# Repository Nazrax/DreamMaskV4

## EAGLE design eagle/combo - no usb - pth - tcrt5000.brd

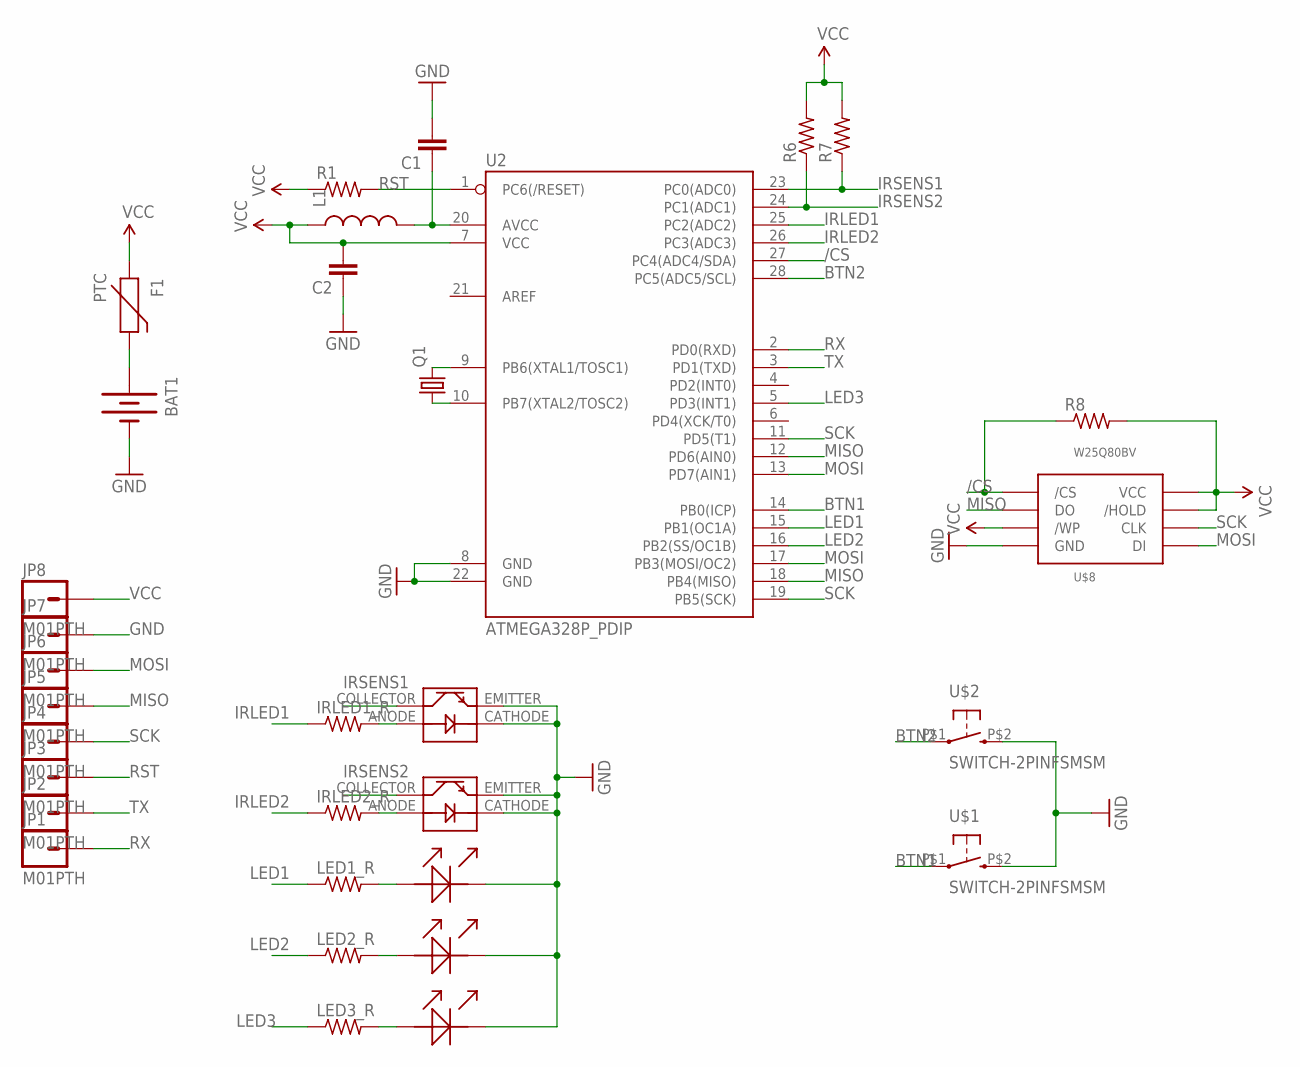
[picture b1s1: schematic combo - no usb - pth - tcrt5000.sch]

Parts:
BAT1: BATTERYBA2032SM; BA2032SM
C1, C2: CAP0805; 0805
F1: PTC; R0805
IRLED1_R, IRLED2_R: R-US_M0805; M0805
JP1, JP2, JP3, JP4, JP5, JP6, JP7, JP8: M01PTH; 1X01
L1: INDUCTOR0805; 0805
LED1_R, LED2_R, LED3_R: R-US_M0805; M0805
Q1: CRYSTALTC26V; TC26V
R1, R6, R7, R8: R-US_M0805; M0805
U2: ATMEGA328P_PDIP; DIL28-3
U$1, U$2: SWITCH-2PINFSMSM; FSMSM-BUTTON
U$3, U$4: IR_SENSORTCRT5000; TCRT5000
U$5, U$6: LEDPTH; LED
U$7: LED0603; 0603
U$8: W25Q80BVSOIC-08; W25Q80BV-SOIC-208MIL

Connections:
/CS: R8.1, U2.27 (PC4(ADC4/SDA)), U$8./CS
BTN1: U2.14 (PB0(ICP)), U$1.P$1 (1)
BTN2: U2.28 (PC5(ADC5/SCL)), U$2.P$1 (1)
GND: BAT1.-, C1.2, C2.1, JP7.1, U2.8 (GND), U2.22 (GND), U$1.P$2 (3), U$2.P$2 (3), U$3.CATHODE (LED-), U$3.EMITTER, U$4.CATHODE (LED-), U$4.EMITTER, U$5.-, U$6.-, U$7.2 (-), U$8.GND
IRLED1: IRLED1_R.1, U2.25 (PC2(ADC2))
IRLED2: IRLED2_R.1, U2.26 (PC3(ADC3))
IRSENS1: R7.1, U2.23 (PC0(ADC0)), U$3.COLLECTOR
IRSENS2: R6.1, U2.24 (PC1(ADC1)), U$4.COLLECTOR
LED1: LED1_R.1, U2.15 (PB1(OC1A))
LED2: LED2_R.1, U2.16 (PB2(SS/OC1B))
LED3: LED3_R.1, U2.5 (PD3(INT1))
MISO: JP5.1, U2.12 (PD6(AIN0)), U2.18 (PB4(MISO)), U$8.DO
MOSI: JP6.1, U2.13 (PD7(AIN1)), U2.17 (PB3(MOSI/OC2)), U$8.DI
unnamed: BAT1.+, F1.2
unnamed: Q1.2, U2.9 (PB6(XTAL1/TOSC1))
unnamed: Q1.1, U2.10 (PB7(XTAL2/TOSC2))
unnamed: C1.1, L1.2, U2.20 (AVCC)
unnamed: LED3_R.2, U$7.1 (+)
unnamed: LED2_R.2, U$6.+
unnamed: LED1_R.2, U$5.+
unnamed: IRLED2_R.2, U$4.ANODE (LED+)
unnamed: IRLED1_R.2, U$3.ANODE (LED+)
RST: JP3.1, R1.2, U2.1 (PC6(/RESET))
RX: JP1.1, U2.2 (PD0(RXD))
SCK: JP4.1, U2.11 (PD5(T1)), U2.19 (PB5(SCK)), U$8.CLK
TX: JP2.1, U2.3 (PD1(TXD))
VCC: C2.2, F1.1, JP8.1, L1.1, R1.1, R6.2, R7.2, R8.2, U2.7 (VCC), U$8./HOLD, U$8./WP, U$8.VCC

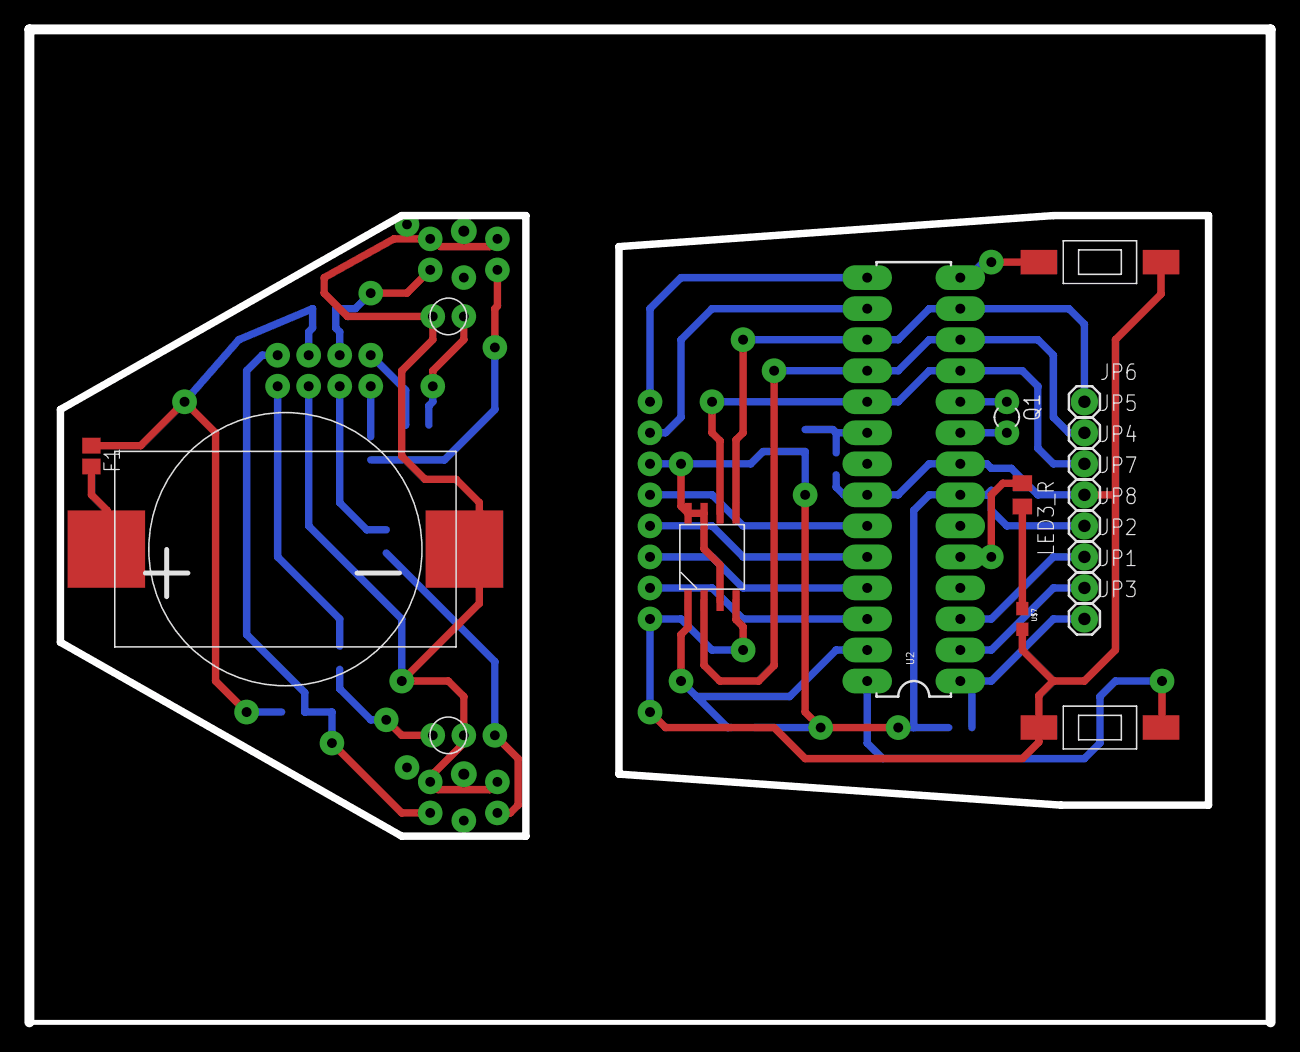
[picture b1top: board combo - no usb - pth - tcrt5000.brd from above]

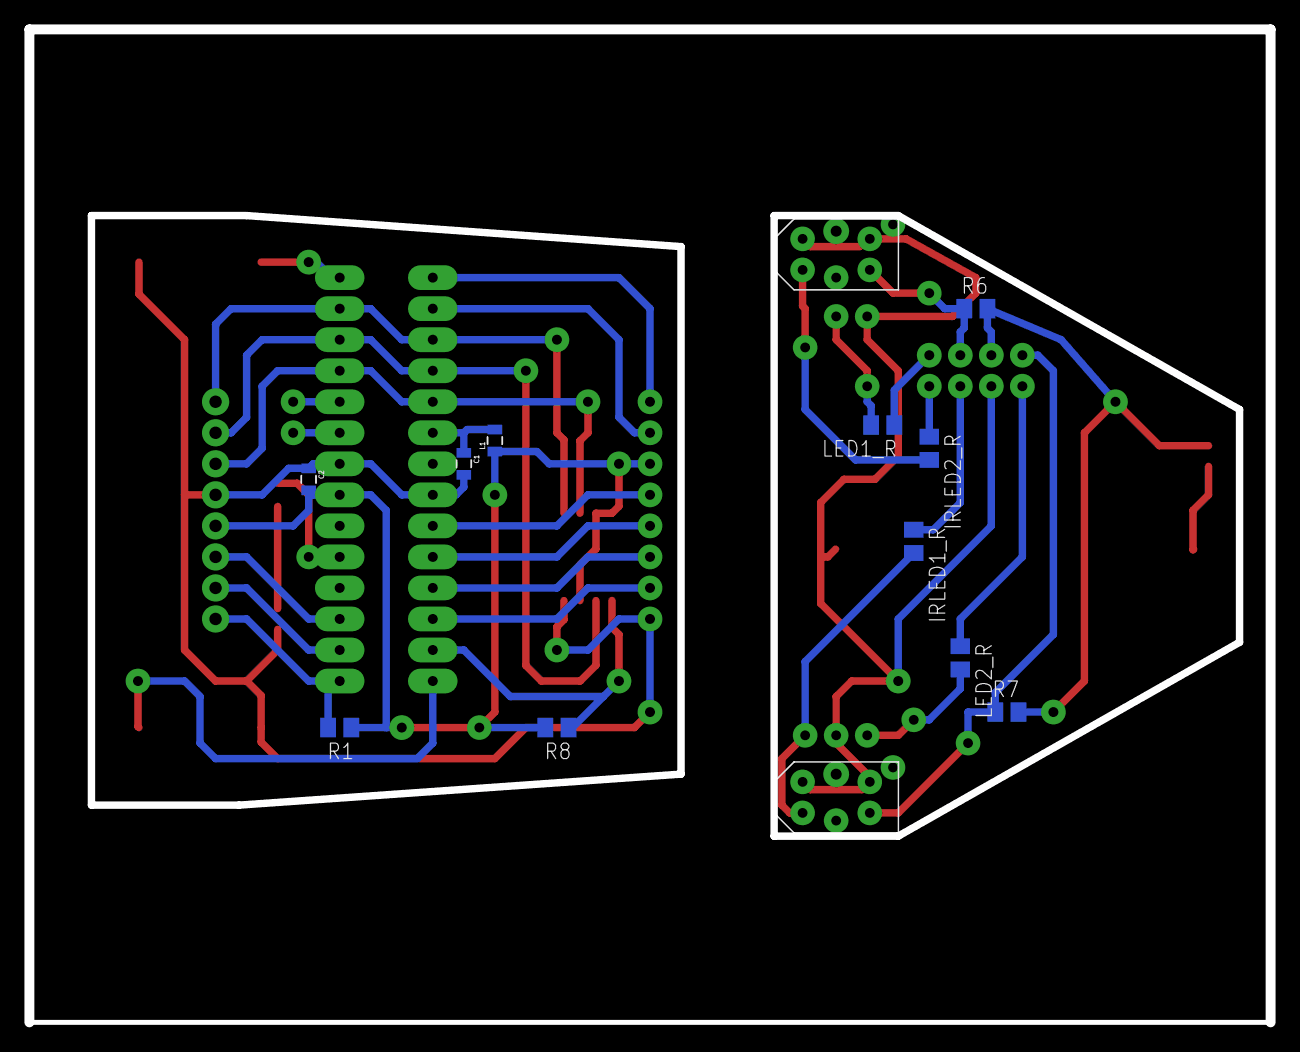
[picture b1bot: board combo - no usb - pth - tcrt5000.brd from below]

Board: 2 copper layers, 101.6 x 81.3 mm, 32 parts (13 on the bottom side), 27 nets.

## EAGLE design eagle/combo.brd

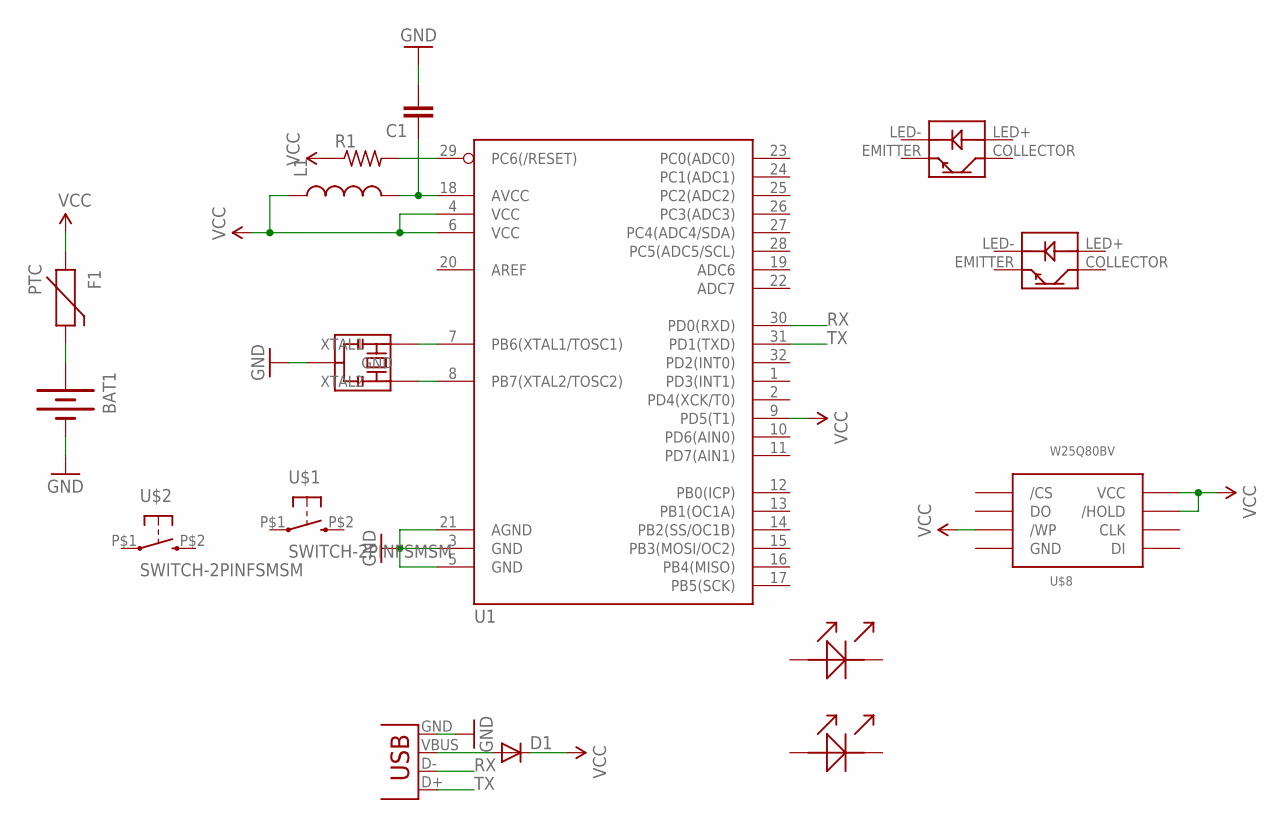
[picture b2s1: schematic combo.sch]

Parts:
BAT1: BATTERYBA2032SM; BA2032SM
C1: CAP0805; 0805
D1: DIODESMA; SMA-DIODE
F1: PTC; R0805
JP9: USB-B; USB-B-PTH
L1: INDUCTOR0805; 0805
R1: R-US_M0805; M0805
U1: ATMEGA328_SMT; TQFP32-08-THIN
U$1, U$2: SWITCH-2PINFSMSM; FSMSM-BUTTON
U$3, U$4: IR_SENSORQRE1113; QRE1113
U$5, U$6: LED0603; 0603
U$7: RESONATOR_W_CAPS; AWSCR-CV
U$8: W25Q80BVSOIC-08; W25Q80BV-SOIC-208MIL

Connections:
GND: BAT1.-, C1.2, JP9.GND, U1.3 (GND), U1.5 (GND), U1.21 (AGND), U$7.GND, U$8.GND
unnamed: BAT1.+, F1.2
unnamed: R1.2, U1.29 (PC6(/RESET))
unnamed: D1.A, JP9.VBUS
unnamed: U1.7 (PB6(XTAL1/TOSC1)), U$7.XTAL1
unnamed: U1.8 (PB7(XTAL2/TOSC2)), U$7.XTAL2
unnamed: C1.1, L1.2, U1.18 (AVCC)
RX: JP9.D-, U1.30 (PD0(RXD))
TX: JP9.D+, U1.31 (PD1(TXD))
VCC: D1.C, F1.1, L1.1, R1.1, U1.4 (VCC), U1.6 (VCC), U1.9 (PD5(T1)), U$8./HOLD, U$8./WP, U$8.VCC

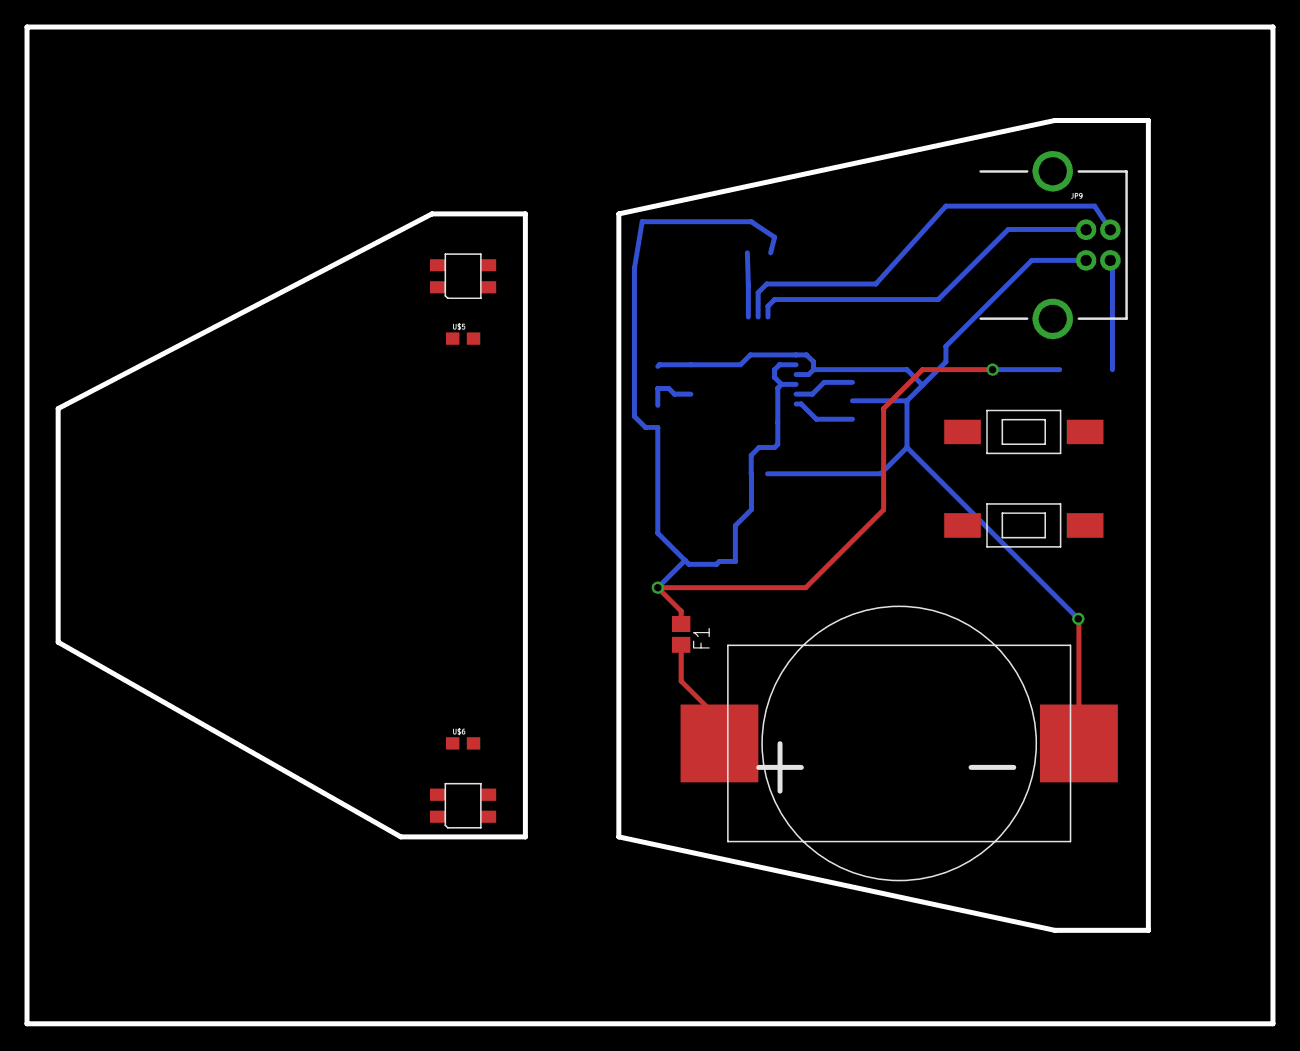
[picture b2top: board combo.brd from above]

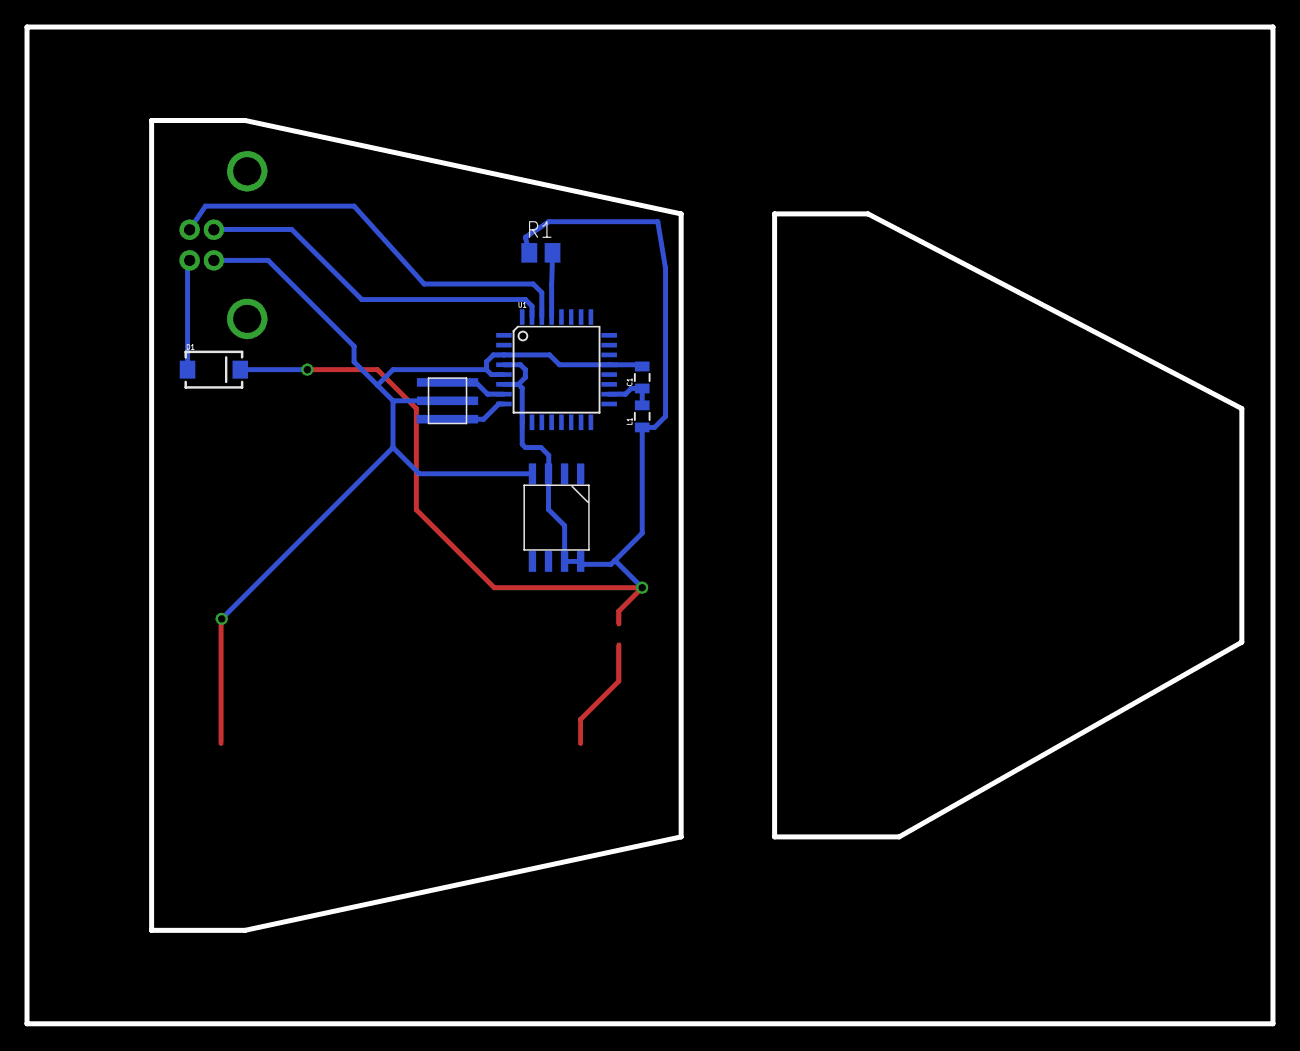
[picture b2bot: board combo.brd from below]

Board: 2 copper layers, 101.6 x 81.3 mm, 16 parts (7 on the bottom side), 10 nets.

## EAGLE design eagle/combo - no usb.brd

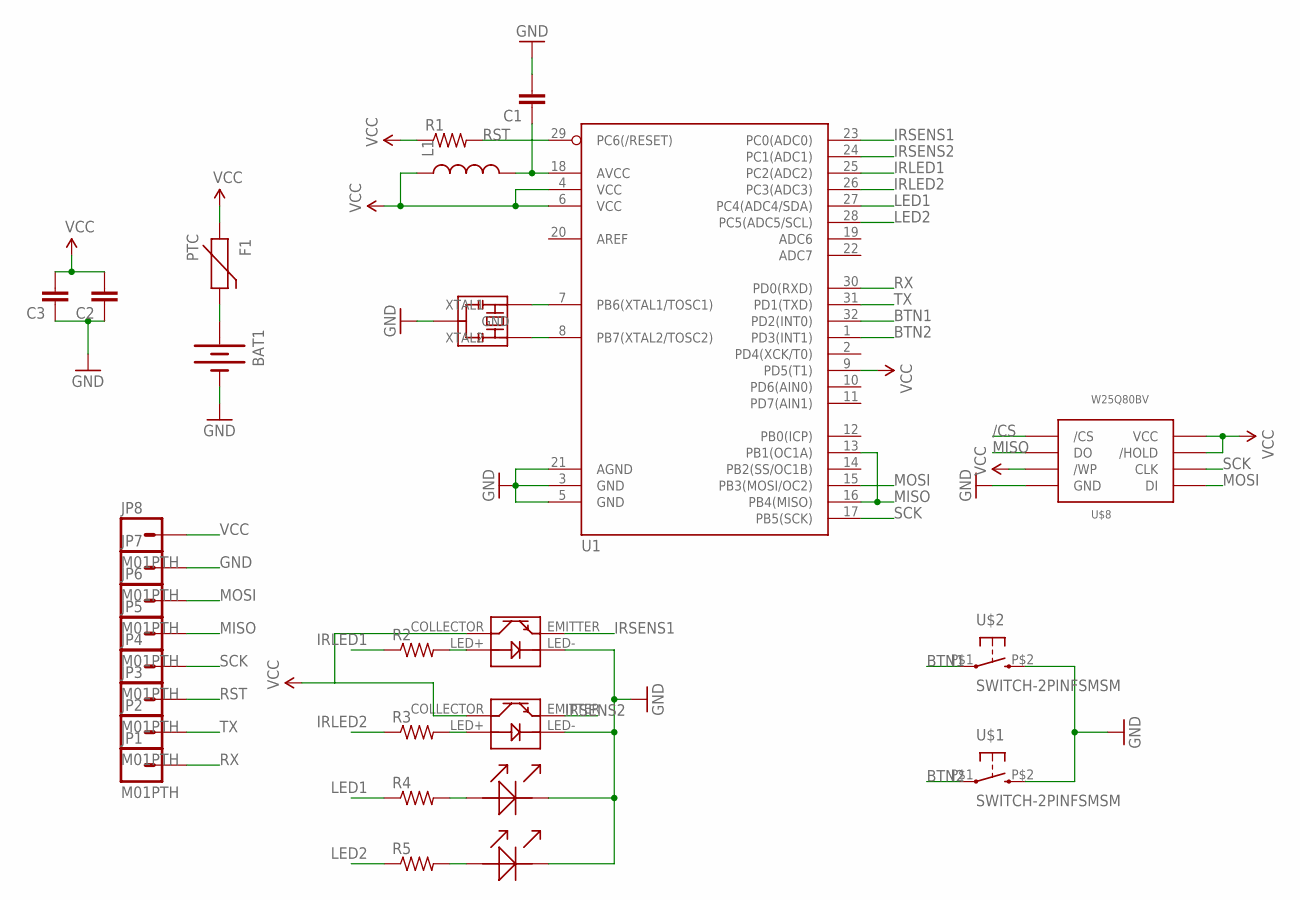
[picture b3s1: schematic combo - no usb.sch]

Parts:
BAT1: BATTERYBA2032SM; BA2032SM
C1, C2, C3: CAP0805; 0805
F1: PTC; R0805
JP1, JP2, JP3, JP4, JP5, JP6, JP7, JP8: M01PTH; 1X01
L1: INDUCTOR0805; 0805
R1, R2, R3, R4, R5: R-US_M0805; M0805
U1: ATMEGA328_SMT; TQFP32-08-THIN
U$1, U$2: SWITCH-2PINFSMSM; FSMSM-BUTTON
U$3, U$4: IR_SENSORQRE1113; QRE1113
U$5, U$6: LED0603; 0603
U$7: RESONATOR_W_CAPS; AWSCR-CV
U$8: W25Q80BVSOIC-08; W25Q80BV-SOIC-208MIL

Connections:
/CS: U$8./CS
BTN1: U1.32 (PD2(INT0)), U$2.P$1 (1)
BTN2: U1.1 (PD3(INT1)), U$1.P$1 (1)
GND: BAT1.-, C1.2, C2.1, C3.1, JP7.1, U1.3 (GND), U1.5 (GND), U1.21 (AGND), U$1.P$2 (3), U$2.P$2 (3), U$3.LED-, U$4.LED-, U$5.2 (-), U$6.2 (-), U$7.GND, U$8.GND
IRLED1: R2.1, U1.25 (PC2(ADC2))
IRLED2: R3.1, U1.26 (PC3(ADC3))
IRSENS1: U1.23 (PC0(ADC0)), U$3.EMITTER
IRSENS2: U1.24 (PC1(ADC1)), U$4.EMITTER
LED1: R4.1, U1.27 (PC4(ADC4/SDA))
LED2: R5.1, U1.28 (PC5(ADC5/SCL))
MISO: JP5.1, U1.13 (PB1(OC1A)), U1.16 (PB4(MISO)), U$8.DO
MOSI: JP6.1, U1.15 (PB3(MOSI/OC2)), U$8.DI
unnamed: BAT1.+, F1.2
unnamed: U1.7 (PB6(XTAL1/TOSC1)), U$7.XTAL1
unnamed: U1.8 (PB7(XTAL2/TOSC2)), U$7.XTAL2
unnamed: C1.1, L1.2, U1.18 (AVCC)
unnamed: R5.2, U$6.1 (+)
unnamed: R4.2, U$5.1 (+)
unnamed: R3.2, U$4.LED+
unnamed: R2.2, U$3.LED+
RST: JP3.1, R1.2, U1.29 (PC6(/RESET))
RX: JP1.1, U1.30 (PD0(RXD))
SCK: JP4.1, U1.17 (PB5(SCK)), U$8.CLK
TX: JP2.1, U1.31 (PD1(TXD))
VCC: C2.2, C3.2, F1.1, JP8.1, L1.1, R1.1, U1.4 (VCC), U1.6 (VCC), U1.9 (PD5(T1)), U$3.COLLECTOR, U$4.COLLECTOR, U$8./HOLD, U$8./WP, U$8.VCC

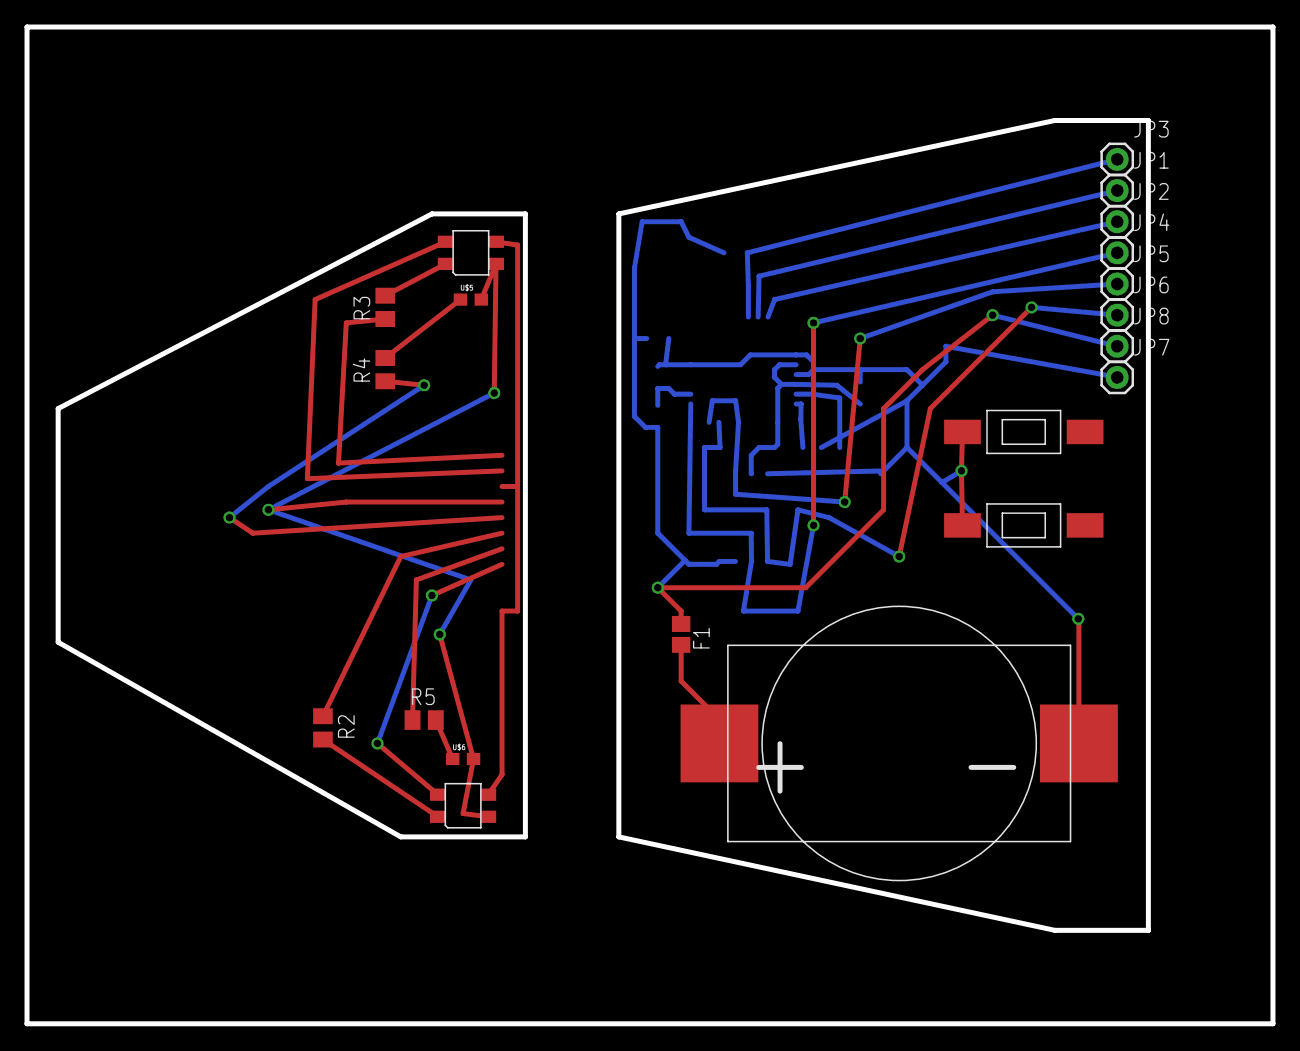
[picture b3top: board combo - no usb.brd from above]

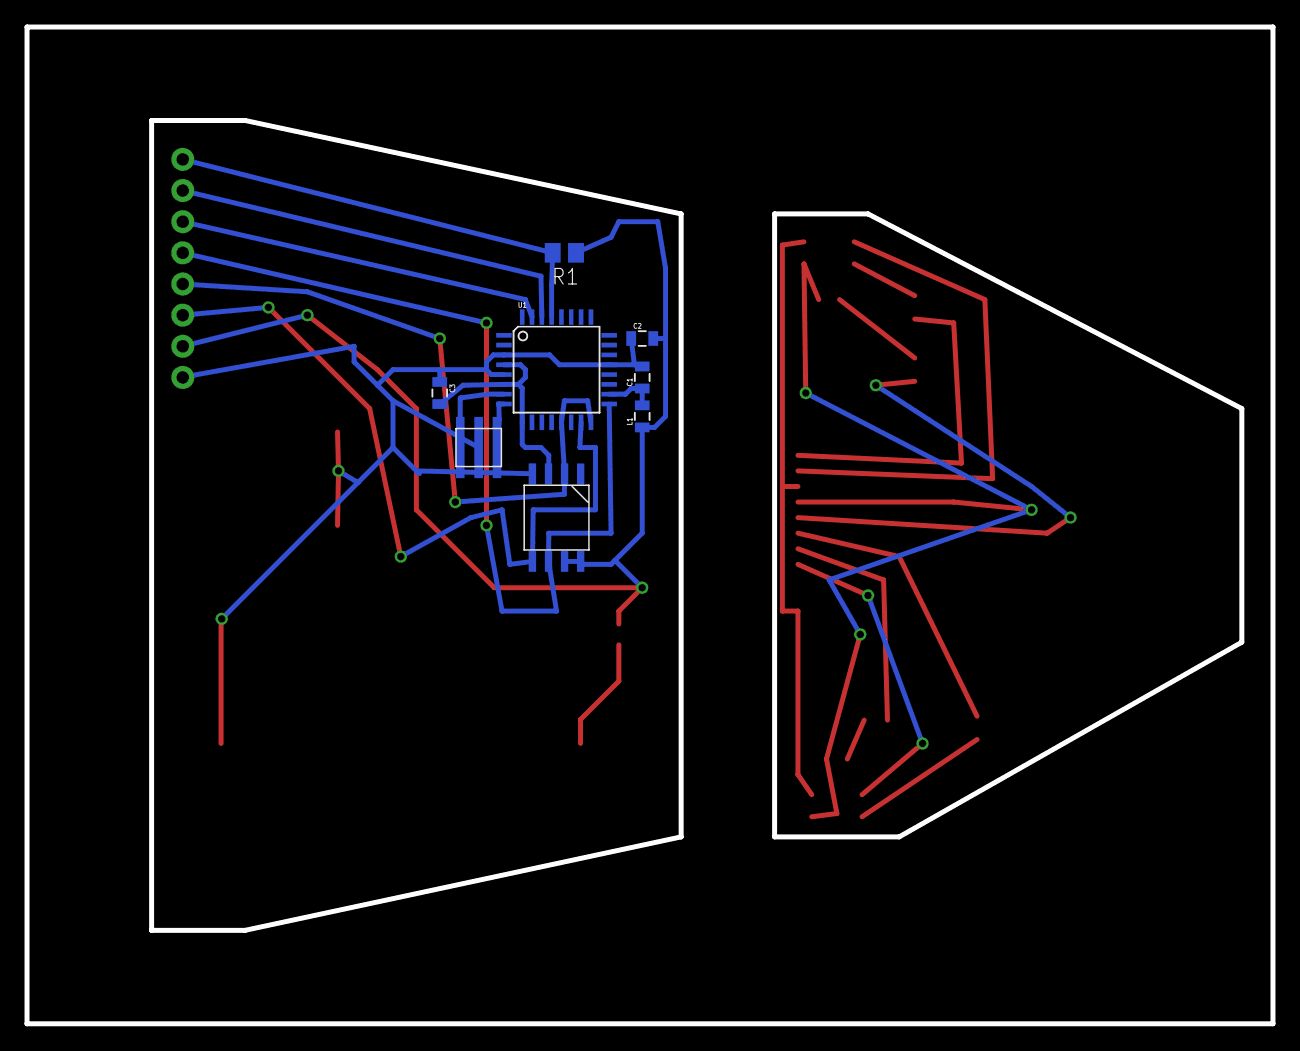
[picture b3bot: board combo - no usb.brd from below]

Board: 2 copper layers, 101.6 x 81.3 mm, 28 parts (8 on the bottom side), 24 nets.

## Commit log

2013-10-30 Initial commit - Eagle badly routed, still needs voltage dividers for sensors
2013-10-30 Remove outdated Eagle files
2013-10-31 Copy DreamMaskV3 source into V4 directory
2013-11-04 Progress routing board
2013-11-04 Good board design
2013-11-22 Add clock calibrator; update pin configurations
2013-12-13 Stuff
2014-03-25 Improve LED handling code, and add LED feedback for testing
2014-03-25 Add Eagle files for the TCRT5000 sensor
2014-03-25 Remove old Eagle files
2014-03-26 Add data scripts
2014-03-31 Progress with morse generator
2014-04-01 Finish initial Morse implementation
2014-11-21 Change programmer timing to be more reliable
2014-11-21 Unknown Eagle change
2014-11-21 Ignore backup and data files
2014-11-21 Add initial voltage detection; add flash verification; improve ADC power usage
2014-11-23 Converts to Lucid Scribe Data with REM channel.
2014-11-24 Added readme.
2014-12-02 Added minimum amount of ticks since last movement.
2014-12-11 Added optional channels with Kalman filters.
2014-12-17 Start to add REM detector to main program (and rename clock_t to myclock_t)
2014-12-17 Add REM detection code
2015-01-27 Add program to run data through detector
2015-01-27 Add dream detection to mask in log-only mode
2015-02-05 Remove duplicate detector_update call
2016-02-03 Many changes, especially for encoding bit flags in eye data
2016-02-22 Added the executable
2016-02-22 Moved the exe for the data converter.

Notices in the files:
parts and their libraries:
SparkFun-Passives: Licensing: CC v3.0 Share-Alike You are welcome to use this library for commercial purposes.
